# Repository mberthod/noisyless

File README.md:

# NOISYLESS — Capteur Environnemental IoT

Firmware ESP32-S3 modulaire pour le capteur environnemental NOISYLESS. Monitoring en temps réel du bruit, de la luminosité, de la qualité d'air (IAQ/CO₂/VOC) et de la présence humaine — transmission MQTT vers le dashboard, OTA over-the-air, LED de statut RGB.

## Capteurs (5 axes)

| Capteur | Pins | Mesure | Module |
|---------|------|--------|--------|
| 🔆 **Luminosité ×2** | GPIO1, GPIO2 (ADC 12-bit) | Lux ambiant, deux directions | `analog_sensors.h` |
| 🎤 **Bruit (micro ×2)** | GPIO3, GPIO4 (ADC 12-bit) | Niveau sonore crête-à-crête (peak-to-peak 50ms) | `analog_sensors.h` |
| 🌡️ **Qualité d'air** | I²C SDA=GPIO35, SCL=GPIO36 | IAQ, CO₂eq, bVOCeq, T°/Hum/Pression compensées, Gas | `bme680_sensor.h` |
| 📡 **Présence radar** | UART Serial1 RX=GPIO18, TX=GPIO17 (256000 bauds) | Cible mobile, cible stationnaire, distance cm | `ld2410_sensor.h` |

### Principe de mesure

- **Lux ×2** : lecture directe `analogRead()` 12-bit, deux photorésistances orientées
- **Micro ×2** : échantillonnage 50ms, calcul de l'amplitude crête-à-crête (`max - min`) via deux électrets analogiques
- **BME680 + BSEC2** : capteur I²C 0x76, mode Ultra Low Power (ULP) — mesure toutes les 3s, calibration IAQ continue via algorithme Bosch BSEC2 (IAQ 0-500, CO₂eq, bVOCeq, T°/Hum/Pression compensées)
- **LD2410** : radar 24 GHz sur UART 256000 bauds, parse les trames binary → détection mouvement + stationnaire + distance

## Architecture firmware (v2.0.0)

```
05_FIRMWARE/
├── src/
│   ├── main.cpp                     # setup(), tâches FreeRTOS
│   ├── sensors/
│   │   ├── bme680_sensor.h/.cpp     # BME680 + BSEC2 (IAQ, CO2, VOC, T/H/P)
│   │   ├── ld2410_sensor.h          # LD2410 radar (présence, distance)
│   │   └── analog_sensors.h         # Lux ×2 + micros ×2 (ADC peak-to-peak)
│   ├── comm/
│   │   └── wifi_mqtt.h              # WiFi (hardcodé) + MQTT (PubSubClient)
│   ├── ota/
│   │   └── ota_manager.h            # OTA HTTP check 60s + download + flash SHA256
│   └── ui/
│       └── led_status.h/.cpp        # LED RGB (actif bas), séquence boot, timings
├── include/
│   ├── wifi_config.h                # SSID + mot de passe WiFi
│   └── credentials.h                # MQTT host/user/pass
└── platformio.ini                   # ESP32-S3, DIO, BSEC2 + LD2410 + PubSubClient
```

### FreeRTOS — 3 tâches

| Tâche | Cœur | Priorité | Stack | Rôle |
|-------|------|----------|-------|------|
| `task_mqtt` | 0 | 1 | 4 Ko | WiFi/MQTT/OTA + publication 10s + LED rouge si WiFi perdu |
| `task_sensors` | 1 | 2 | 4 Ko | BME680 tick + LD2410 tick + Analog (50ms) |
| `task_led` | 0 | 0 | 2 Ko | Timings LED (vert boot 1s, flash publish 200ms) |

Les données sont partagées via `SharedData` protégé par `SemaphoreHandle_t` mutex.

### Séquence LED

| État | LED | Durée |
|------|-----|-------|
| Boot | 🔴 Rouge fixe | ~1s |
| WiFi en cours | 🔵 Bleu fixe | Jusqu'à connexion |
| Version | 🔵×N clignotements | N = 3ᵉ chiffre version (ex: v2.0.**0** → 10 flashs) |
| Connecté | 🟢 Vert fixe | 1s |
| Publication MQTT OK | 🟢 Flash vert | 200ms |
| Idle | ⚫ Éteinte | — |
| WiFi perdu | 🔴 Rouge fixe | Jusqu'à reconnexion |

**Mapping GPIO** : LED_R=GPIO12, LED_G=GPIO13, LED_B=GPIO14. Actif bas : `LOW = allumé`.

## Payload MQTT

Topic : `esp32/noisyless/{MAC}/datas`

```json
{
  "product": "noisyless_env",
  "client_code": "client_demo",
  "device_id": "NL-A1B2C3D4E5F6",
  "fw_version": "2.0.0",

  "lux1_raw": 2048,
  "lux2_raw": 1890,
  "sound_mic1_pp": 295,
  "sound_mic2_pp": 266,

  "presence": true,
  "distance_cm": 120,

  "temp_comp_c": 22.40,
  "hum_comp_pct": 48.30,
  "pressure_pa": 101325,
  "iaq": 25.0,
  "co2eq_ppm": 450.0,
  "bvoc_eq_ppm": 0.50,
  "gas_ohms": 50000,
  "iaq_accuracy": 3,
  "stab_status": 1,
  "run_in_status": 1,

  "rssi_dbm": -58,
  "uptime_s": 3600
}
```

**Champs optionnels** : si le BME680 n'est pas détecté, les champs IAQ/CO₂/VOC/T°/Hum/Pression sont omis. Si le LD2410 n'est pas détecté, `presence` et `distance_cm` restent à `false`/`0`.

## Déploiement OTA — Workflow complet

### Prérequis

- PlatformIO (`pio --version`)
- Accès SSH au serveur Hetzner : `noisyless@91.99.26.43`
- Firmware servi par nginx depuis `/opt/noisyless/static/firmware/` sur le port 80
- WiFi hardcodé dans `include/wifi_config.h`

### 1. Modifier le firmware

```bash
cd 05_FIRMWARE
```

Sources à modifier :
- `src/main.cpp` — `FW_VERSION`, logique métier
- `include/wifi_config.h` — SSID + mot de passe WiFi
- `include/credentials.h` — host/user/pass MQTT

**Incrémenter `FW_VERSION`** dans `main.cpp` :
```cpp
#define FW_VERSION "2.0.1"  // ← changer ici
```

### 2. Builder

```bash
pio run -e esp32dev
```

Sortie : `.pio/build/esp32dev/firmware.bin` (~972 Ko avec BSEC2+LD2410)

**Config PlatformIO** (`platformio.ini`) :
- `board = esp32-s3-devkitc-1`
- `board_build.flash_size = 8MB`
- `board_build.psram_type = disabled`
- `board_build.flash_mode = dio`
- `board_build.flash_freq = 40m`
- `build_flags = -D ARDUINO_USB_CDC_ON_BOOT=1`
- `lib_deps = PubSubClient, ld2410, bsec2, BME68x`

### 3. Calculer le SHA256

```bash
sha256sum .pio/build/esp32dev/firmware.bin
```

### 4. Déployer sur le serveur

```bash
# Copier le binaire
scp .pio/build/esp32dev/firmware.bin noisyless@91.99.26.43:/opt/noisyless/static/firmware/

# Mettre à jour le manifest OTA
ssh noisyless@91.99.26.43 'cat > /opt/noisyless/static/firmware/latest.json << EOF
{"version":"2.0.1","url":"http://91.99.26.43/firmware/firmware.bin","sha256":"LE_HASH_ICI"}
EOF'
```

### 5. Vérifier

```bash
# Manifest
curl -s http://91.99.26.43/firmware/latest.json

# Binaire (200 OK)
curl -sI http://91.99.26.43/firmware/firmware.bin | head -3

# SHA256 côté serveur
ssh noisyless@91.99.26.43 'sha256sum /opt/noisyless/static/firmware/firmware.bin'
```

### 6. Propagation OTA

Chaque module checke le manifest **toutes les 60s**. Si `version != FW_VERSION` :
1. Téléchargement `.bin` (30s timeout)
2. Vérification SHA256
3. `Update.begin()` → flash
4. `ESP.restart()`

**Rollback automatique** : si le firmware ne boote pas, le bootloader ESP32-S3 restaure la partition précédente.

### 7. Surveillance

```bash
# Devices et versions
ssh noisyless@91.99.26.43 "docker compose -f /opt/noisyless/docker-compose.yml exec -T timescaledb psql -U noisyless -d noisyless -c 'SELECT device_id, firmware_version, status, last_seen FROM noisyless.devices ORDER BY last_seen DESC;'"

# Logs env-ingest
ssh noisyless@91.99.26.43 "docker compose -f /opt/noisyless/docker-compose.yml logs --tail=30 env-ingest | grep -E 'fw_version|device_id'"
```

### Flash USB direct (recovery)

```bash
pio run -e esp32dev -t upload

# Bootloop → full erase
pio run -e esp32dev -t erase && pio run -e esp32dev -t upload
```

## Architecture système

```
┌──────────────────────────┐     MQTT      ┌─────────────────┐     SQL      ┌──────────────┐
│  ESP32-S3 (×N)           │──────────────▶│  Hetzner VPS     │─────────────▶│ TimescaleDB   │
│  WiFi + MQTT + OTA       │   port 1883   │  mosquitto       │             │               │
│  lux×2 + mic×2           │               │  env-ingest      │    HTTP     │ devices       │
│  BME680/BSEC2 IAQ        │               │  api             │◀────────────│ measurements │
│  LD2410 présence         │◀──────────────│  nginx (static)  │             └──────────────┘
│  LED RGB statut          │   OTA HTTP:80  │                  │
└──────────────────────────┘               └─────────────────┘
```

## Pièges connus

- **ESP32-S3 flash mode** : S3-MINI-1 est QIO natif mais GPIO12/14 sont sur le bus SPI → utiliser DIO 40 MHz. Sans ça, les LEDs ne fonctionnent pas.
- **Partitions OTA** : `default.csv` suffit. `custom_partitions.csv` peut causer des bootloops si l'otadata est corrompue.
- **WiFiManager NVS** : les credentials WiFiManager survivent au reflash. Utiliser `esptool.py erase_flash` si on change de WiFi.
- **LED jaune** : toujours `led_off()` avant de changer de couleur (actif bas, rouge+vert simultanés = jaune).
- **SHA256 mismatch** : OTA silencieusement ignoré si le hash manifest ≠ hash binaire. Vérifier avec `curl | sha256sum`.
- **BSEC2 calibration** : l'IAQ met ~5 min à se stabiliser au premier boot (`run_in_status` = 1). L'accuracy monte progressivement de 0 à 3.
- **LD2410 baud rate** : 256000 obligatoire. Le constructeur documente 115200 mais le firmware usine est à 256000.
- **BME680 I²C** : scanne 0x76 puis 0x77. Si le capteur est en mode sleep (broche MODE flottante), il ne répond pas. GPIO37 doit être LOW.
- **Taille flash** : BSEC2 + BME68x + LD2410 = ~972 Ko / 1310 Ko dispo (74%). Compiler sans PSRAM. Vérifier `board_build.psram_type = disabled`.

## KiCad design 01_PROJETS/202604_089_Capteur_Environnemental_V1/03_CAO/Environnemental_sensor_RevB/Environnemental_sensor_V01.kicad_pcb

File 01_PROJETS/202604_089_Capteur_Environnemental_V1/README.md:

# Environmental Sensor Firmware Documentation

## Overview

This documentation describes the firmware for an ESP32-S3 based environmental sensor system. The system is designed to monitor various environmental parameters including air quality, light levels, sound levels, and presence detection. The firmware is built using the Arduino framework and FreeRTOS for task management.

## System Architecture

The firmware is organized into several key components:

1. **Sensor Management**: Handles reading data from various environmental sensors
2. **Network Communication**: Manages WiFi connectivity and data transmission to a server
3. **Memory Management**: Monitors and optimizes memory usage
4. **Alert System**: Detects and reports significant environmental changes
5. **OTA Updates**: Supports over-the-air firmware updates

## FreeRTOS Task Structure

The firmware uses FreeRTOS to manage concurrent operations through the following tasks:

- **Memory Task**: Monitors memory usage and performs periodic defragmentation
- **Sensor Task**: Reads data from sensors at regular intervals
- **Network Task**: Handles all network communications
- **Button Task**: Monitors the physical button for user interactions

## Key Features

- Real-time environmental monitoring
- Automatic data transmission to a central server
- Offline data storage with automatic transmission when connectivity is restored
- Memory leak detection and prevention
- Automatic firmware updates
- Alert system for significant environmental changes

## Getting Started

To use this firmware:

1. Configure your credentials in `credentials.h`
2. Upload the firmware to your ESP32-S3 device
3. The device will automatically connect to WiFi and begin monitoring

## Memory Management

The firmware includes sophisticated memory management features:

- Periodic memory status logging
- Memory leak detection
- Automatic defragmentation
- NVS (Non-Volatile Storage) cleaning

## Network Communication

The firmware supports:

- Automatic WiFi connection and reconnection
- HTTP communication with a central server
- Retry mechanisms for failed transmissions
- Offline data storage

## Alert System

The alert system can detect:

- Device removal from its mounting
- Significant environmental changes
- System errors and warnings

## OTA Updates

The firmware supports over-the-air updates:

- Automatic update checking
- Secure update process
- Version management

## Dependencies

- Arduino Framework
- FreeRTOS
- WiFi Library
- HTTPClient Library
- ArduinoJson Library
- Preferences Library

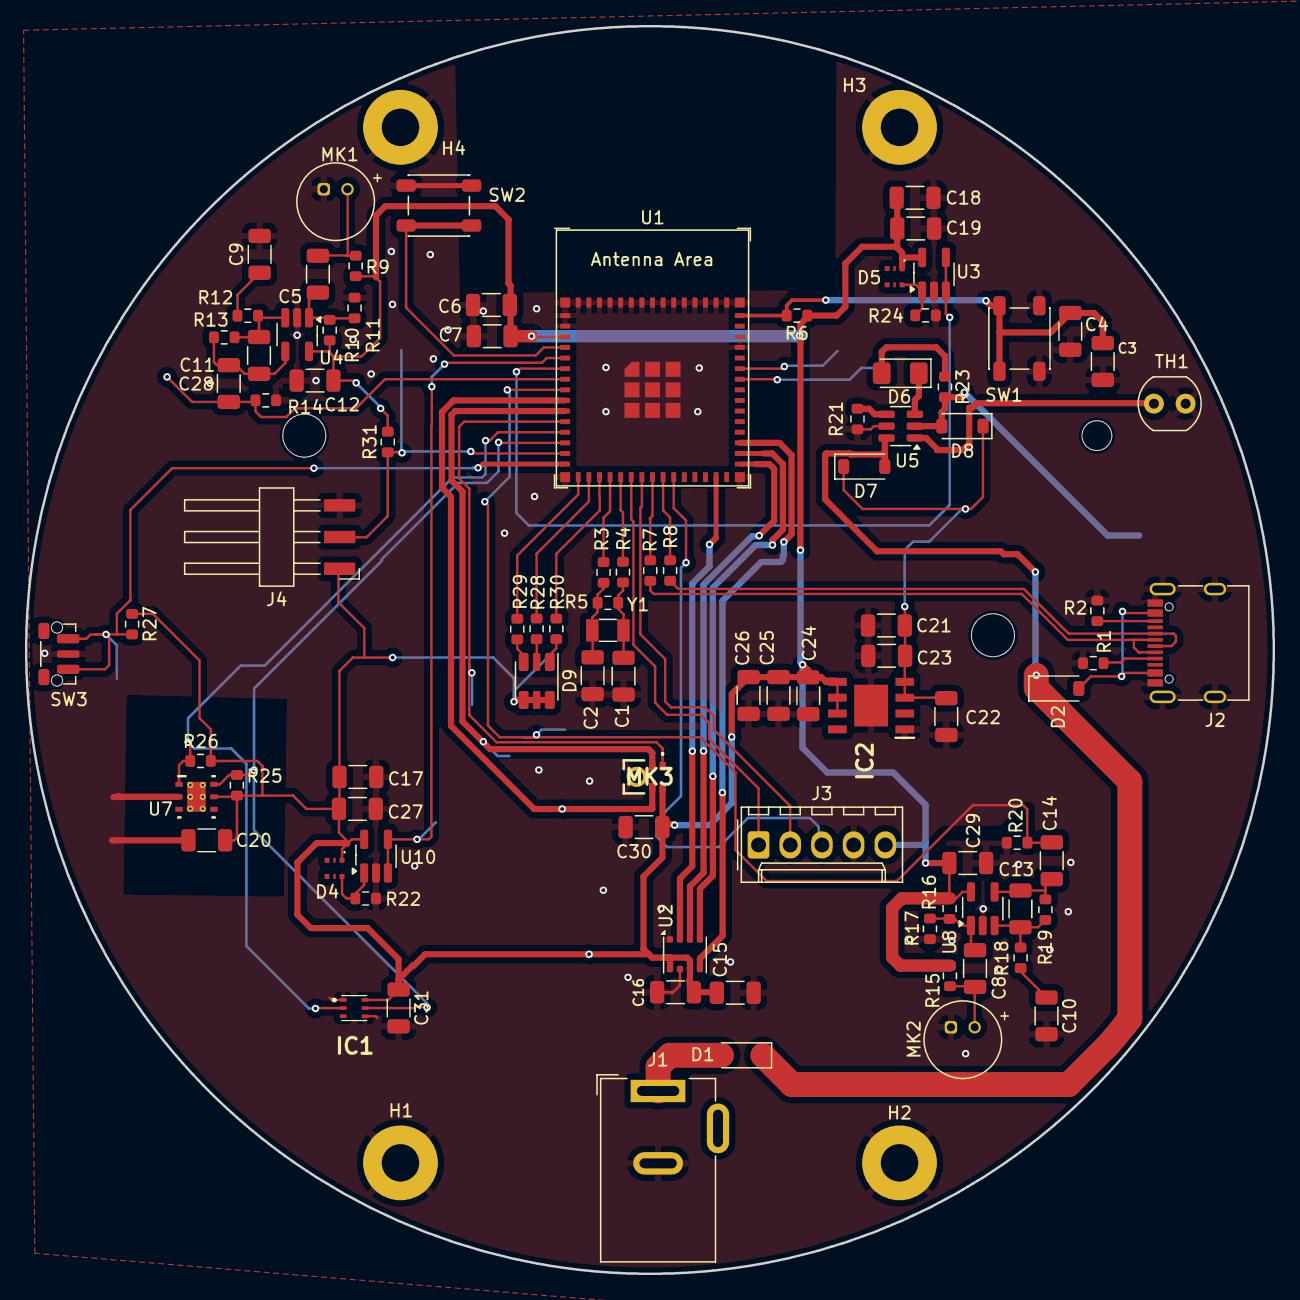
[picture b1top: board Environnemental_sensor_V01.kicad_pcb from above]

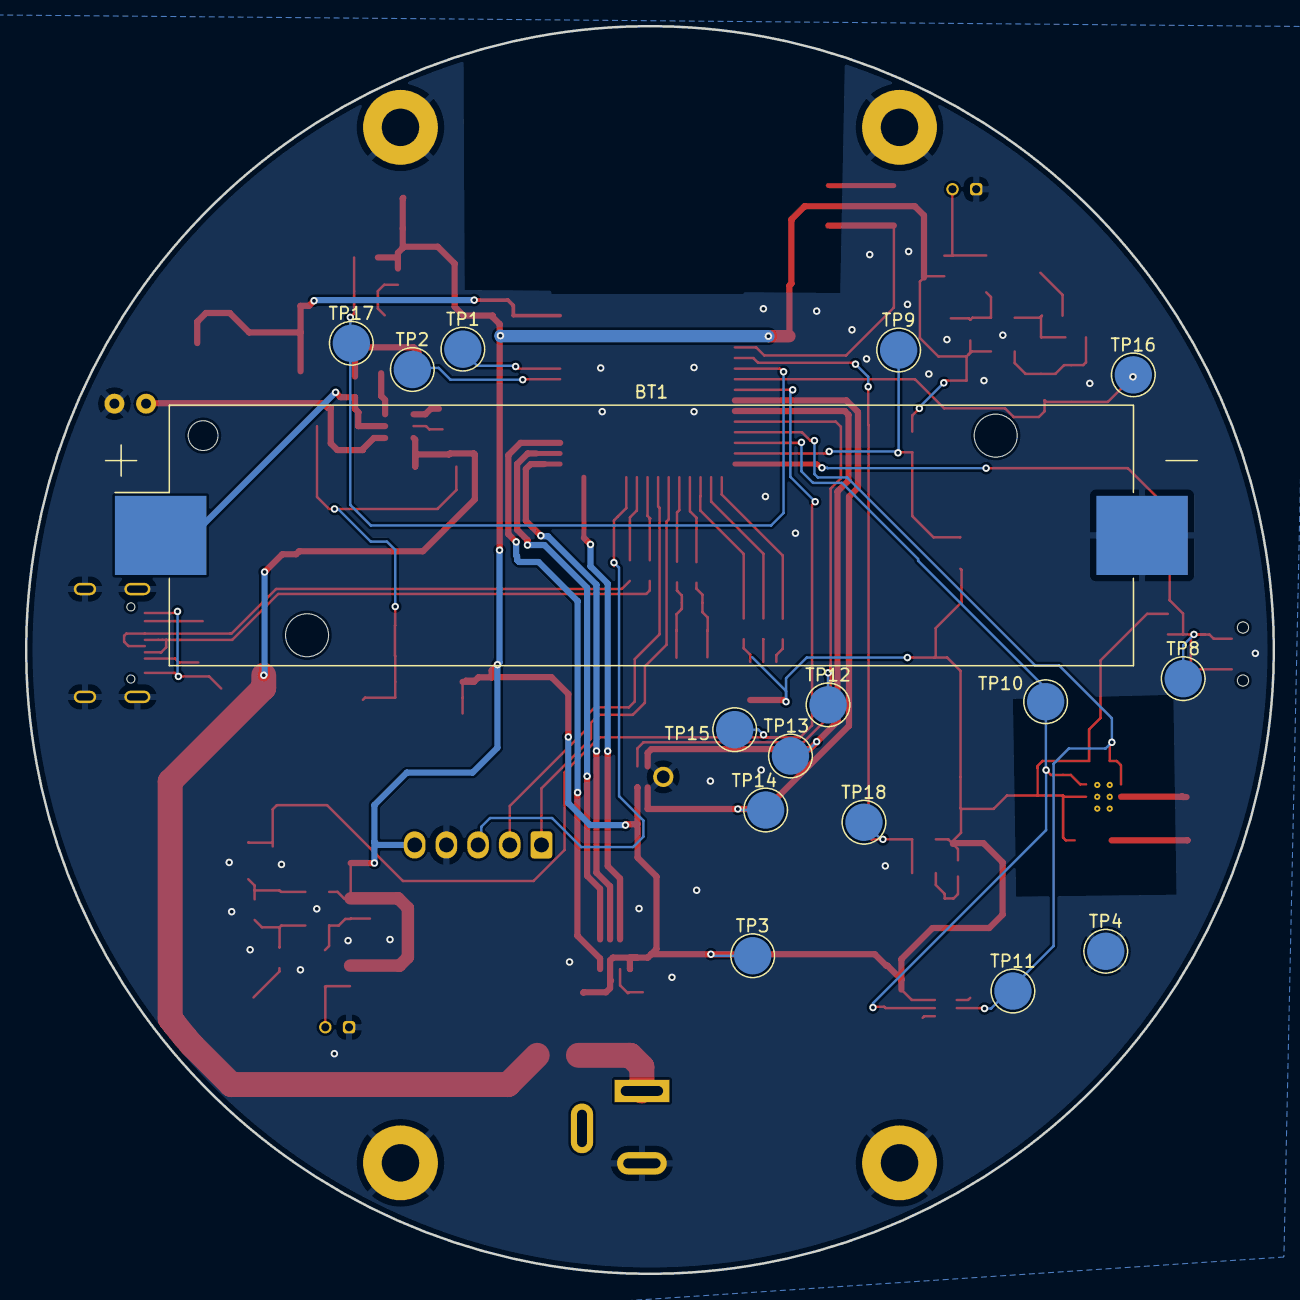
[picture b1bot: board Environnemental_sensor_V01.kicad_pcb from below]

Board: 2 copper layers, 100.0 x 100.0 mm, 112 parts (16 on the bottom side), 61 nets.

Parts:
BT1: Battery_Cell; BatteryHolder_Keystone_1042_1x18650
C1, C2: 12pF; C_1206_3216Metric
C3, C4, C7, C12, C15, C16, C17, C19, C20, C26, C29, C30, C31: 100nF; C_1206_3216Metric
C5, C8, C18, C21, C22, C23, C24, C25, C27: 330nF; C_1206_3216Metric
C6: 22uF; C_1206_3216Metric
C9, C10: 47uF; C_1206_3216Metric
C11, C13: 120pF; C_1206_3216Metric
C14, C28: 3.3uF; C_1206_3216Metric
D1, D2, D7, D8: 1N5819HW-7-F; D_SOD-123
D4, D5: APDS-9005-020; PHODET_APDS-9005-020
D6: LED; LED_1206_3216Metric_Pad1.42x1.75mm_HandSolder
D9: Inolux_IN-P55TATRGB; LED_ROHM_SMLVN6
H1, H2, H3, H4: MountingHole_Pad; MountingHole_3mm_Pad
IC1: VEML6030
IC2: AP7362-33SP-13; SOIC127P600X150-9N
J1: Jack-DC; BarrelJack_Wuerth_6941xx301002
J2: USB_C_Receptacle_USB2.0_16P; USB_C_Receptacle_G-Switch_GT-USB-7010ASV
J3: Conn_01x05_Pin; Molex_KK-254_AE-6410-05A_1x05_P2.54mm_Vertical
J4: Conn_01x03_Pin; Harwin_M20-89003xx_1x03_P2.54mm_Horizontal
MK1, MK2: Microphone_Condenser; POM-2244P-C3310-2-R
MK3: T3902
R1, R2, R21, R23: 5k1; R_0603_1608Metric
R3, R4, R7, R8: 0R; R_0603_1608Metric
R5: 1M; R_0603_1608Metric
R6, R13, R14, R19, R20, R27: 10k; R_0603_1608Metric
R9, R15: 5.9k; R_0603_1608Metric
R10, R11, R16, R17: 200k; R_0603_1608Metric
R12, R18: 787R; R_0603_1608Metric
R22, R24: 1K; R_0603_1608Metric
R25, R26, R31: 4.99k; R_0603_1608Metric
R28, R29, R30: 1k; R_0603_1608Metric
SW1: EN; SW_SPST_PTS647_Sx38
SW2: BOOT; SW_SPST_PTS647_Sx38
SW3: SW_Push; SW_Push_1P1T-MP_NO_Horizontal_Alps_SKRTLAE010
TH1: Thermistor_NTC; R_LDR_4.9x4.2mm_P2.54mm_Vertical
TP1, TP2, TP3, TP4, TP8, TP9, TP10, TP11, TP12, TP13, TP14, TP15, TP16, TP17, TP18: TestPoint; TestPoint_Pad_D3.0mm
U1: ESP32-S3-MINI-1
U2: BME680; Bosch_LGA-8_3x3mm_P0.8mm_ClockwisePinNumbering
U3, U4, U8, U10: LMV321; SOT-23-5_HandSoldering
U5: BQ21040DBV; SOT-23-6
U7: HDC1080DMBR; DMB0006A
Y1: 32.768KHz; Crystal_SMD_3215-2Pin_3.2x1.5mm

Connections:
1_WIRE: J4.2, R31.1, TP9.1, U1.14 (GPIO10/TOUCH10/ADC1_CH9/FSPICS0/FSPIIO4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)
+5V: D1.1 (K), D2.1 (K), D7.2 (A), U5.6 (VIN)
CLK: MK3.4 (CLK), TP14.1, U1.9 (GPIO5/TOUCH5/ADC1_CH4)
CSB: U1.29 (SPIIO5/GPIO34/FSPICS0/SUBSPICS0), U2.2 (CSB)
DATA: MK3.1 (DATA), TP12.1, U1.11 (GPIO7/TOUCH7/ADC1_CH6)
GND: BT1.2 (-), C1.1, C2.1, C3.1, C4.1, C6.2, C7.1, C9.2, C10.2, C12.2, C15.2, C16.1, C17.2, C18.2, C19.2, C20.1, C21.1, C22.1, C23.1, C24.1, C25.1, C26.1, C27.2, C29.2, C30.1, C31.2, H1.1, H2.1, H3.1, H4.1, IC1.1 (GND), IC1.4 (ADD), IC2.1 (GND), IC2.9 (EP), J1.2, J2.A1 (GND), J2.A12 (GND), J2.B1 (GND), J2.B12 (GND), J2.S1 (SHIELD), J3.4, J4.3, MK1.1 (-), MK2.1 (-), MK3.3 (GND), R1.2, R2.2, R11.2, R14.2, R17.2, R20.2, R21.2, R22.1, R24.1, SW1.1, SW2.2, SW3.2, TH1.2, TP4.1, U1.1 (GND), U1.2 (GND), U1.42 (GND), U1.43 (GND), U1.46 (GND), U1.47 (GND), U1.48 (GND), U1.49 (GND), U1.50 (GND), U1.51 (GND), U1.52 (GND), U1.53 (GND), U1.54 (GND), U1.55 (GND), U1.56 (GND), U1.57 (GND), U1.58 (GND), U1.59 (GND), U1.60 (GND), U1.61 (GND), U1.62 (GND), U1.63 (GND), U1.64 (GND), U1.65 (GND), U2.1 (GND), U2.7 (GND), U3.2 (V-), U4.2 (V-), U5.5 (GND), U7.2 (GND), U8.2 (V-), U10.2 (V-)
LED_B: R30.1, U1.18 (GPIO14/TOUCH14/ADC2_CH3/FSPIWP/FSPIDQS/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)
LED_G: R29.1, U1.16 (GPIO12/TOUCH12/ADC2_CH1/FSPICLK/FSPIIO6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)
LED_R: R28.1, U1.17 (GPIO13/TOUCH13/ADC2_CH2/FSPIQ/FSPIIO7/S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)
LUX_sensor1: TP18.1, U1.5 (GPIO1/TOUCH1/ADC1_CH0), U10.3 (-), U10.4
LUX_sensor2: TP17.1, U1.6 (GPIO2/TOUCH2/ADC1_CH1), U3.3 (-), U3.4
MIC1: C28.2, R14.1, TP16.1, U1.7 (GPIO3/TOUCH3/ADC1_CH2)
MIC2: C14.2, R20.1, TP15.1, U1.8 (GPIO4/TOUCH4/ADC1_CH3)
unnamed: BT1.1 (+), D8.2 (A), R23.2, U5.2 (OUT)
unnamed: C1.2, R4.2, R5.2, Y1.1
unnamed: C2.2, R3.1, R5.1, Y1.2
unnamed: C9.1, R12.1
unnamed: C10.1, R18.1
unnamed: C11.2, C28.1, R13.2, U4.4
unnamed: C13.2, C14.1, R19.2, U8.4
unnamed: D1.2 (A), J1.1
unnamed: D2.2 (A), J2.A4 (VBUS), J2.A9 (VBUS), J2.B4 (VBUS), J2.B9 (VBUS)
unnamed: D4.6 (OUT), R22.2, U10.1 (+)
unnamed: D5.6 (OUT), R24.2, U3.1 (+)
unnamed: D6.2 (A), R23.1
unnamed: D6.1 (K), U5.3 (~CHG)
unnamed: C21.2, C22.2, C23.2, D7.1 (K), D8.1 (K), IC2.3 (IN_1), IC2.4 (IN_2)
unnamed: D9.1 (KB), R30.2
unnamed: D9.3 (KG), R29.2
unnamed: D9.2 (KR), R28.2
unnamed: J2.A5 (CC1), R1.1
unnamed: J2.B5 (CC2), R2.1
unnamed: C5.1, MK1.2 (+), R9.2
unnamed: C8.1, MK2.2 (+), R15.2
unnamed: C3.2, C4.2, R6.2, SW1.2, U1.45 (EN)
unnamed: SW2.1, U1.4 (GPIO0/BOOT)
unnamed: R3.2, U1.19 (GPIO15/U0RTS/ADC2_CH4/XTAL_32K_P)
unnamed: R4.1, U1.20 (GPIO16/U0CTS/ADC2_CH5/XTAL_32K_N)
unnamed: R7.2, U1.23 (GPIO19/U1RTS/ADC2_CH8/CLK_OUT2/USB_D-)
unnamed: R8.2, U1.24 (GPIO20/U1CTS/ADC2_CH9/CLK_OUT1/USB_D+)
unnamed: TP1.1, U1.40 (U0RXD/GPIO44/CLK_OUT2)
unnamed: TP2.1, U1.39 (U0TXD/GPIO43/CLK_OUT1)
unnamed: C5.2, R10.2, R11.1, U4.1 (+)
unnamed: C11.1, R12.2, R13.1, U4.3 (-)
unnamed: R21.1, U5.4 (ISET)
unnamed: TH1.1, U5.1 (TS)
unnamed: C8.2, R16.2, R17.1, U8.1 (+)
unnamed: C13.1, R18.2, R19.1, U8.3 (-)
OUT: J3.3, U1.25 (GPIO21)
RX: J3.1, U1.21 (GPIO17/U1TXD/ADC2_CH6)
SCK: U1.32 (SPIIO7/GPIO36/FSPICLK/SUBSPICLK), U2.4 (SCK)
SCL: IC1.5 (SCL), R25.1, TP10.1, U1.13 (GPIO9/TOUCH9/ADC1_CH8/FSPIHD/SUBSPIHD), U7.6 (SCL)
SDA: IC1.2 (SDA), R26.1, TP11.1, U1.12 (GPIO8/TOUCH8/ADC1_CH7/SUBSPICS1), U7.1 (SDA)
SDI: U1.31 (SPIIO6/GPIO35/FSPID/SUBSPID), U2.3 (SDI)
SDO: U1.33 (SPIDQS/GPIO37/FSPIQ/SUBSPIQ), U2.5 (SDO)
SELECT: MK3.2 (SELECT), TP13.1, U1.10 (GPIO6/TOUCH6/ADC1_CH5)
SW_OPEN: R27.2, SW3.1, TP8.1, U1.15 (GPIO11/TOUCH11/ADC2_CH0/FSPID/FSPIIO5/S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)
TX: J3.2, U1.22 (GPIO18/U1RXD/ADC2_CH7/CLK_OUT3)
USBD+: J2.A6 (D+), J2.B6 (D+), R8.1
USBD-: J2.A7 (D-), J2.B7 (D-), R7.1
VCC: C6.1, C7.2, C12.1, C15.1, C16.2, C17.1, C18.1, C19.1, C20.2, C24.2, C25.2, C26.2, C27.1, C29.1, C30.2, C31.1, D4.1 (VCC), D5.1 (VCC), D9.4 (AG), D9.5 (AR), D9.6 (AB), IC1.6 (VDD), IC2.5 (OUT_1), IC2.6 (OUT_2), IC2.7 (OUT_3), J3.5, J4.1, MK3.5 (VDD), R6.1, R9.1, R10.1, R15.1, R16.1, R25.2, R26.2, R27.1, R31.2, TP3.1, U1.3 (3V3), U2.6 (VDDIO), U2.8 (VDD), U3.5 (V+), U4.5 (V+), U7.5 (VDD), U8.5 (V+), U10.5 (V+)

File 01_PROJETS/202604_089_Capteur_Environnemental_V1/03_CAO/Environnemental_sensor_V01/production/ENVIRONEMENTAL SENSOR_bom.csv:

'Reference','Value','Datasheet','Description','Footprint','Qty','DNP','MPN'
'BT1','Battery_Cell','https://www.lcsc.com/datasheet/lcsc_datasheet_2204021730_MYO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,'Single-cell battery','Battery:BatteryHolder_Keystone_1042_1x18650','1','','C2988620'
'C1,C2','12pF','https://www.lcsc.com/datasheet/lcsc_datasheet_2304140030_FH-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,'Unpolarized capacitor','Capacitor_SMD:C_1206_3216Metric','2','','C1886'
'C3,C4,C7,C12,C15,C16,C17,C19,C20,C26,C29,C30,C31','100nF','https://www.lcsc.com/datasheet/lcsc_datasheet_2304140030_FH-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,'Unpolarized capacitor','Capacitor_SMD:C_1206_3216Metric','13','','C110255'
'C5,C8,C18,C21,C22,C23,C24,C25,C27','330nF','https://www.lcsc.com/datasheet/lcsc_datasheet_2304140030_YAG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,'Unpolarized capacitor, small symbol','Capacitor_SMD:C_1206_3216Metric','9','','C274377'
'C6','22uF','https://www.lcsc.com/datasheet/lcsc_datasheet_2304140030_SAN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,'Polarized capacitor, small symbol','Capacitor_SMD:C_1206_3216Metric','1','','C2835562'
'C9,C10','47uF','https://www.lcsc.com/datasheet/lcsc_datasheet_1810201233_Mur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,'Polarized capacitor, small symbol','Capacitor_SMD:C_1206_3216Metric','2','','C94034'
'C11,C13','120pF','https://www.lcsc.com/datasheet/lcsc_datasheet_2403201121_Chi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,'Unpolarized capacitor, small symbol','Capacitor_SMD:C_1206_3216Metric','2','','C5186921'
'C14,C28','3.3uF','https://www.lcsc.com/datasheet/lcsc_datasheet_2304140030_TDK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,'Unpolarized capacitor, small symbol','Capacitor_SMD:C_1206_3216Metric','2','','C76663'
'D1,D2,D7,D8','1N5819HW-7-F','https://4donline.ihs.com/images/VipMasterIC/IC/DIOD/DIOD-S-A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,'Diode Schottky, 40 V, 1 A, Une, SOD-123, 2 Broche(s), 750 mV','Diode_SMD:D_SOD-123','4','','C82544'
'D4,D5','APDS-9005-020','https://www.lcsc.com/datasheet/lcsc_datasheet_2403281708_Bro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,'','custom_footprint:PHODET_APDS-9005-020','2','','C2649497'
'D6','LED','~','Light emitting diode','LED_SMD:LED_1206_3216Metric_Pad1.42x1.75mm_HandSolder','1','','C84270'
'D9','Inolux_IN-P55TATRGB','https://www.inolux-corp.com/datasheet/SMDLED/RGB%20Top%20Vie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,'Inolux RGB LED, PLCC-6','LED_SMD:LED_ROHM_SMLVN6','1','','C784540'
'IC1','VEML6030','https://www.vishay.com/docs/84366/veml6030.pdf','VEML6030 Vishay, Ambient Light Sensor, Ambient Light to Digital Data I2C 6-Pin','custom_footprint:VEML6030','1','','C132182'
'IC2','AP7362-33SP-13','https://www.diodes.com//assets/Datasheets/AP7362.pdf','LDO Voltage Regulators LDO CMOS HiCurr SO-8 1.5A LowQ Adj 190mV','custom_footprint:SOIC127P600X150-9N','1','','C780775'
'J1','Jack-DC','https://www.lcsc.com/datasheet/lcsc_datasheet_2308221657_BOO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,'DC Barrel Jack','Connector_BarrelJack:BarrelJack_Wuerth_6941xx301002','1','','C16214'
'J2','USB_C_Receptacle_USB2.0_16P','https://www.usb.org/sites/default/files/documents/usb_type-c.zip','USB 2.0-only 16P Type-C Receptacle connector','Connector_USB:USB_C_Receptacle_G-Switch_GT-USB-7010ASV','1','','C2988369'
'J3','Conn_01x05_Pin','~','Generic connector, single row, 01x05, script generated','Connector_Molex:Molex_KK-254_AE-6410-05A_1x05_P2.54mm_Vertical','1','',''
'J4','Conn_01x03_Pin','~','Generic connector, single row, 01x03, script generated','Connector_Harwin:Harwin_M20-89003xx_1x03_P2.54mm_Horizontal','1','','C5242196'
'MK1,MK2','Microphone_Condenser','https://www.lcsc.com/datasheet/lcsc_datasheet_2304140030_ING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,'Condenser microphone','Sensor_Audio:POM-2244P-C3310-2-R','2','','C233939'
'MK3','T3902','http://invensense.tdk.com/wp-content/uploads/2020/05/DS-0003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,'MEMS Microphones 126 dB SPL AOP MEMS Microphone','T3902','1','','C237403'
'R1,R2,R21,R23','5k1','https://www.lcsc.com/datasheet/lcsc_datasheet_2206010116_UNI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,'Resistor','Resistor_SMD:R_0603_1608Metric','4','','C23186'
'R3,R4,R7,R8','0R','https://www.lcsc.com/datasheet/lcsc_datasheet_2206010130_UNI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,'Resistor','Resistor_SMD:R_0603_1608Metric','4','','C21189'
'R5','1M','https://www.lcsc.com/datasheet/lcsc_datasheet_2206010130_UNI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,'Resistor','Resistor_SMD:R_0603_1608Metric','1','','C22935'
'R6,R13,R14,R19,R20,R27','10k','https://www.lcsc.com/datasheet/lcsc_datasheet_2206010045_UNI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,'Resistor','Resistor_SMD:R_0603_1608Metric','6','','C25804'
'R9,R15','5.9k','https://www.lcsc.com/datasheet/lcsc_datasheet_2206010116_UNI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,'Resistor','Resistor_SMD:R_0603_1608Metric','2','','C23071'
'R10,R11,R16,R17','200k','https://www.lcsc.com/datasheet/lcsc_datasheet_2206010045_UNI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,'Resistor','Resistor_SMD:R_0603_1608Metric','4','','C25811'
'R12,R18','787R','https://www.lcsc.com/datasheet/lcsc_datasheet_2304140030_YAG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,'Resistor','Resistor_SMD:R_0603_1608Metric','2','','C137683'
'R22,R24','1K','https://www.lcsc.com/datasheet/lcsc_datasheet_2206010130_UNI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,'Resistor','Resistor_SMD:R_0603_1608Metric','2','','C21190'
'R25,R26,R31','4.99k','https://www.lcsc.com/datasheet/lcsc_datasheet_2304140030_YAG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,'Resistor','Resistor_SMD:R_0603_1608Metric','3','','C114621'
'R28,R29,R30','1k','https://www.lcsc.com/datasheet/lcsc_datasheet_2206010130_UNI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,'Resistor','Resistor_SMD:R_0603_1608Metric','3','','C21190'
'SW1','EN','https://4donline.ihs.com/images/VipMasterIC/IC/CKCI/CKCI-S-A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,'Push button switch, generic, four pins','Button_Switch_SMD:SW_SPST_PTS647_Sx38','1','','C2689502'
'SW2','BOOT','https://4donline.ihs.com/images/VipMasterIC/IC/CKCI/CKCI-S-A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,'Push button switch, generic, four pins','Button_Switch_SMD:SW_SPST_PTS647_Sx38','1','','C2689502'
'SW3','SW_Push','https://www.lcsc.com/datasheet/lcsc_datasheet_1809191932_ALP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,'Push button switch, generic, two pins','Button_Switch_SMD:SW_Push_1P1T-MP_NO_Horizontal_Alps_SKRTLAE010','1','','C110293'
'TH1','Thermistor_NTC','https://www.lcsc.com/datasheet/lcsc_datasheet_2304140030_Nan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,'Temperature dependent resistor, negative temperature coefficient','OptoDevice:R_LDR_4.9x4.2mm_P2.54mm_Vertical','1','','C13879'
'TP1,TP2,TP3,TP4,TP8,TP9,TP10,TP11,TP12,TP13,TP14,TP15,TP16,TP17,TP18','TestPoint','~','test point','TestPoint:TestPoint_Pad_D3.0mm','15','DNP',''
'U1','ESP32-S3-MINI-1','https://www.espressif.com/sites/default/files/documentation/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,'Smallsized module supporting 2.4 GHz WiFi (802.11 b/g/n) and Bluetooth ® 5 (LE) Built around ESP32S3 series of SoCs, Xtensa ® dualcore 32bit LX7 microprocessor Flash up to 8 MB, optional 2 MB PSRAM in chip package 39 GPIOs, rich set of peripherals Onboard PCB antenna or external antenna connector','PCM_Espressif:ESP32-S3-MINI-1','1','','C2913206'
'U2','BME680','https://ae-bst.resource.bosch.com/media/_tech/media/datashee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,'4-in-1 sensor, gas, humidity, pressure, temperature, I2C and SPI interface, 1.71-3.6V, LGA-8','Package_LGA:Bosch_LGA-8_3x3mm_P0.8mm_ClockwisePinNumbering','1','','C125972'
'U3,U4,U8,U10','LMV321','http://www.ti.com/lit/ds/symlink/lmv324.pdf','Low-Voltage Rail-to-Rail Output Operational Amplifiers, SOT-23-5/SC-70-5','Package_TO_SOT_SMD:SOT-23-5_HandSoldering','4','','C395459'
'U5','BQ21040DBV','https://www.ti.com/lit/ds/symlink/bq21040.pdf','Single cell, 0.8A Li-Ion/Li-Po linear charge management controller, up to 30V input, 4.2V charge voltage, Open-Drain Status Output, Temperature sense input, SOT-23-6','Package_TO_SOT_SMD:SOT-23-6','1','','C202311'
'U7','HDC1080DMBR','https://www.lcsc.com/datasheet/lcsc_datasheet_1810271112_Tex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,'','custom_footprint:DMB0006A','1','','C82227'
'Y1','32.768KHz','http://www.farnell.com/datasheets/3929147.pdf','Cristal, 32.768 kHz, CMS, 3.2mm x 1.5mm, 12.5 pF, 20 ppm, RT3215 Series','Crystal:Crystal_SMD_3215-2Pin_3.2x1.5mm','1','','C97606'

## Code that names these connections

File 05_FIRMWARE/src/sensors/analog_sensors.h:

/**
 * analog_sensors.h — Capteurs analogiques NOISYLESS v2.0.0
 * 
 * Lux ×2 :   ADC 12-bit sur GPIO1 (AIN1), GPIO2 (AIN2)
 * Micro ×2 : ADC 12-bit peak-to-peak sur GPIO3 (AIN3), GPIO4 (AIN4)
 * 
 * Usage :
 *   AnalogSensors sensors;
 *   sensors.init();
 *   sensors.read();                    // bloque 50ms
 *   uint16_t lux1 = sensors.lux1_raw;
 *   uint16_t mic1 = sensors.mic1_pp;
 */

#ifndef ANALOG_SENSORS_H
#define ANALOG_SENSORS_H

#include <Arduino.h>

#define PIN_LUX1_AIN 1
#define PIN_LUX2_AIN 2
#define PIN_MIC1     3
#define PIN_MIC2     4
#define ANALOG_WINDOW_MS 50  // durée échantillonnage micros

struct AnalogReadings {
  uint16_t lux1_raw = 0;
  uint16_t lux2_raw = 0;
  uint16_t mic1_pp  = 0;   // peak-to-peak
  uint16_t mic2_pp  = 0;
};

class AnalogSensors {
public:
  void init() {
    analogReadResolution(12);
  }
  
  const AnalogReadings& read() {
    auto t0 = millis();
    
    _data.lux1_raw = analogRead(PIN_LUX1_AIN);
    _data.lux2_raw = analogRead(PIN_LUX2_AIN);
    
    // Échantillonnage micros sur 50ms pour calculer le peak-to-peak
    uint16_t min1 = 4095, max1 = 0;
    uint16_t min2 = 4095, max2 = 0;
    
    while (millis() - t0 < ANALOG_WINDOW_MS) {
      uint16_t s1 = analogRead(PIN_MIC1);
      uint16_t s2 = analogRead(PIN_MIC2);
      if (s1 < min1) min1 = s1;
      if (s1 > max1) max1 = s1;
      if (s2 < min2) min2 = s2;
      if (s2 > max2) max2 = s2;
      delay(1);
    }
    
    _data.mic1_pp = (max1 > min1) ? max1 - min1 : 0;
    _data.mic2_pp = (max2 > min2) ? max2 - min2 : 0;
    
    return _data;
  }
  
  const AnalogReadings& last() const { return _data; }

private:
  AnalogReadings _data;
};

#endif // ANALOG_SENSORS_H

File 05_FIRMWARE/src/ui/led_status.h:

/**
 * led_status.h — Module LED RGB NOISYLESS v2.0.0
 * 
 * Brochage :  LED_R=GPIO12, LED_G=GPIO13, LED_B=GPIO14
 * Logique   :  actif bas (LOW = allumée, HIGH = éteinte)
 * 
 * Séquence de boot :
 *   1. rouge fixe       → boot en cours
 *   2. bleu fixe        → tentative WiFi
 *   3. bleu ×N flashs   → affiche le 3ᵉ chiffre de la version (v2.0.0 → 0 flash)
 *   4. vert fixe 1s     → connecté
 *   5. éteinte          → idle
 * 
 * Runtime :
 *   - WiFi perdu → rouge fixe
 *   - Publication MQTT réussie → flash vert 200ms
 * 
 * Usage :
 *   led_init();            // setup()
 *   led_set(LED_RED);      // loop() si WiFi perdu
 *   led_flash_green();     // après mqtt.publish() réussi
 *   led_boot_sequence();   // après WiFi connecté (bloque ~1.5s)
 */

#ifndef LED_STATUS_H
#define LED_STATUS_H

#include <Arduino.h>

// Pins (actif bas)
#define PIN_LED_R 12
#define PIN_LED_G 13
#define PIN_LED_B 14

// Couleurs
typedef enum {
  LED_OFF   = 0,
  LED_RED   = 1,
  LED_GREEN = 2,
  LED_BLUE  = 3,
  LED_YELLOW = 4,  // rouge+vert simulé (flash rapide)
  LED_PURPLE = 5   // rouge+bleu pour OTA
} led_color_t;

// Timings
#define LED_BLINK_MS      150   // durée flash version
#define LED_GREEN_HOLD_MS 1000  // vert après connexion
#define LED_PUB_FLASH_MS  200   // flash vert publication

/**
 * Initialise les pins LED en OUTPUT, éteintes.
 */
void led_init();

/**
 * Allume une couleur (éteint les autres avant).
 */
void led_set(led_color_t color);

/**
 * Éteint toutes les LED.
 */
void led_off();

/**
 * Affiche le 3ᵉ chiffre de la version via N flashs bleus.
 * Bloquant (~N × 2 × LED_BLINK_MS ms).
 * @param version  chaîne "2.0.0" → 0 flash
 */
void led_show_version(const char* version);

/**
 * Séquence complète après connexion WiFi :
 * blink version → vert 1s → off.
 * Bloquant (~2s max).
 */
void led_boot_sequence(const char* version);

/**
 * Flash vert 200ms pour signaler une publication MQTT réussie.
 * Non-bloquant (juste une impulsion).
 */
void led_flash_green();

/**
 * Gère les timings LED (vert boot 1s, flash publish 200ms).
 * À appeler régulièrement (~20ms) depuis une tâche FreeRTOS.
 */
void led_tick();

#endif // LED_STATUS_H

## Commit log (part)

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2025-12-08 first commit repertoire
2026-05-24 firmware: update OTA manifest URL to mberthod/noisyless/main/ota/stable.json
2026-05-24 ota: initial stable.json manifest for firmware updates
2026-05-24 ota: add stable.json manifest for firmware updates
2026-05-24 feat: OTA forced at boot + MQTT working
2026-05-24 fix: mqtt-ingest asyncio thread-safe queue + heatmap_agg_5min table
2026-05-24 chore: gitignore SSL accounts and KiCad history
2026-05-24 fix: convert 089 from broken gitlink to regular folder
2026-05-24 refactor: align NOISYLESS on MATLOG structure (01_PROJETS/)
    - Move 202604_089_* and 202605_091_* into 01_PROJETS/
    - Move deployment code (backend/frontend/web/services/_infra/nginx/ota/visu/
    noisyless-deployment) into 091/_commun/ (shared by the 3 firmware variants)
    - Move deployment docs (BACKEND_PLAN, DEPLOYMENT_*, TODO, TASKS_ORDERED,
    PROMPTS, tasks.json, README_DEPLOYMENT) into 091/_commun/docs/
    - Move OSRAM TMF8829 datasheet into 091/docs/datasheets/
2026-05-24 feat: add node-radar-60ghz firmware components (ESP-IDF)
    - Add components: config, mesh, mqtt, ms72sf1 (radar sensor driver)
    - Add platformio.ini, partitions.csv, sdkconfig.defaults
    - Update main.c with radar heatmap implementation
    Project 091 - HeatMap Presence firmware
2026-05-26 sync: rapatriement code API production + cahier de recette
    - auth.py (432 lignes): auth JWT, register, login, magic-link, reset password
    - customer.py (62 lignes): gestion clients
    - devices.py (179 lignes): CRUD devices
    - emails.py (55 lignes): SMTP OVH
    - pilot.py (165 lignes): programme pilote
    - shop.py (87 lignes): endpoint checkout Stripe
2026-05-26 feat: kit de démarrage agent Hermes (.hermes/)
    - SOUL.md: instructions système minimales (IP, design, biz model, pièges)
    - skills/noisyless-heatmap: règles firmware/hardware #091 + refs
    - skills/noisyless-deployment: procédures déploiement + refs (stripe, nginx, ota...)
    - backlog/todo.json: 28 tâches avec statuts (21 done, 6 blocked, 1 error)
    - backlog/logs/: 23 logs d'exécution horodatés
    - knowledge/: fiches clients + projets NOISYLESS (#045, #089, #091)
2026-05-27 firmware v1.0.8: LED rouge si WiFi perdu, OTA déployé sur 4 modules
2026-05-27 docs: README complet — capteurs, OTA, LED, architecture, pièges
2026-05-27 firmware v2.0.0: architecture modulaire FreeRTOS — BME680/BSEC2, LD2410, OTA, LED
2026-05-27 docs: README v2.0.0 — architecture modulaire, 5 capteurs, FreeRTOS
2026-05-27 ota: v1.1.0 — manifest pointe vers VPS (noisyless.com/firmware/), SHA256 vérifié
2026-05-27 ota: v0.0.1 — firmware production, I2C fix, LED OTA, check every 10min
2026-05-27 ota: v0.0.2 — test OTA, LED bleue 3s
2026-05-28 feat: v0.0.3 - fix double exception crash during OTA
    - WiFiClientSecure heap-allocated (new) instead of stack
    - g_otaMutex semaphore to prevent concurrent OTA calls
    - g_otaRunning flag to track OTA state
    - errLeds() non-blocking (blink once then continue)
    - All variables declared before goto ota_cleanup (C++ compliance)
    SHA256: d4346d9452dde7186495a99e70b9602fbc6a7a5ad5d1a1d9895527b8c400e268
2026-05-28 chore: update stable.json to v0.0.3
2026-05-29 sync: VPS production v1 snapshot (29 mai 2026)
    - Snapshot complet du VPS Hetzner 91.99.26.43 vers _live/
    - admin.py, env-ingest (3 fichiers) ajoutés à _infra
    - auth.py, devices.py, main.py mis à jour (VPS version live)
    - platform.html, admin.html, dashboard.html + pages HeatMap
    - produits/, cas-usage/, comparatif/, technologie/ complétés
    - firmware/stable.json, latest.json
2026-05-29 firmware v0.0.1: WiFiManager captive portal custom NOISYLESS + fix Guru (BME680 absent safe) + publish immédiat + OTA VPS
2026-05-29 firmware v0.0.2: Doxygen complet + détection auto I2C BME680 (0x76/0x77)
2026-05-29 firmware v0.0.3: portal 60s, fallback TP-Link reboot, boucle infinie si pas de WiFi
2026-05-29 firmware v0.0.4: LED violette pendant OTA + check toutes les 2 minutes
2026-05-29 firmware v0.0.5: fix WDT reset avec yield() pendant download OTA
2026-05-29 firmware v0.0.6: fix NVS write mode + yield() WDT WiFi loops
2026-05-29 firmware v0.0.7: fix stack overflow task_mqtt (6144->8192 bytes)
2026-05-29 firmware v0.0.4: LED version display: FW_VERSION 0.0.4 → 4 blue flashes
2026-05-29 firmware v0.0.8: OTA check interval restored to 2min, timeout reduced to 90s
2026-05-29 led_status: version display logic and bugfix
2026-05-29 firmware v0.0.9: OTA timeout 90s, check only when no OTA running
2026-05-29 firmware v0.0.9: OTA timeout 90s, version check fix
2026-05-29 firmware v0.0.9: OTA fix: remove g_otaRunning=true before boot check
2026-05-29 firmware v0.0.10: Test OTA from v0.0.10 to v0.0.10 - should fail gracefully
2026-05-29 firmware v0.0.10: Test OTA version bump
2026-05-29 firmware v0.0.10: OTA check boot fix, LED version display
2026-05-29 firmware v0.0.10: OTA check preserved with comments
2026-05-29 firmware v0.0.11: Test OTA deployment chain
2026-05-30 infra: add deployment scripts, legal docs, platform page, and env-ingest service
